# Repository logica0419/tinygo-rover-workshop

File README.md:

# tinygo-rover-workshop

TinyGo Rover Workshop 〜走れ！Tiny号

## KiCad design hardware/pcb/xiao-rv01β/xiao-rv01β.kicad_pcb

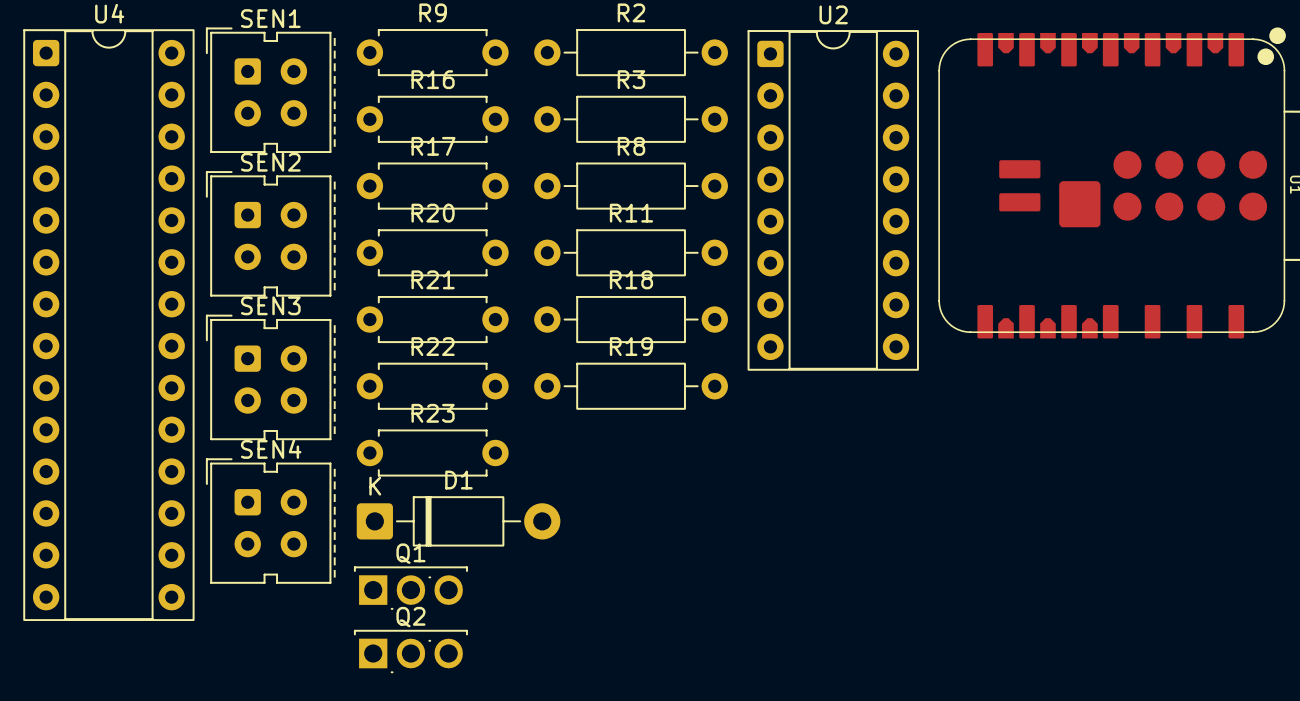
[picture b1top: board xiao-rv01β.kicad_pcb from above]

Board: 2 copper layers, 23 parts (0 on the bottom side), 21 nets, no tracks yet.

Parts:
D1: TVS 5V; D_DO-41_SOD81_P10.16mm_Horizontal
Q1, Q2: P-Ch -12V/-6A; TO-251-3_Vertical
R2, R19: 100kΩ; R_Axial_DIN0207_L6.3mm_D2.5mm_P10.16mm_Horizontal
R3, R8, R11: 22kΩ; R_Axial_DIN0207_L6.3mm_D2.5mm_P10.16mm_Horizontal
R9, R16, R17, R20, R23: 2.2kΩ; R_Axial_DIN0207_L6.3mm_D2.5mm_P7.62mm_Horizontal
R18: 33kΩ; R_Axial_DIN0207_L6.3mm_D2.5mm_P10.16mm_Horizontal
R21, R22: 1kΩ; R_Axial_DIN0207_L6.3mm_D2.5mm_P7.62mm_Horizontal
SEN1, SEN2, SEN3, SEN4: LBR-123F; Vishay_CNY70
U1: XIAO-ESP32-S3-Plus; XIAO-ESP32-S3-Plus-SMD
U2: MCP3208; DIP-16_W7.62mm_Socket
U4: MCP23S17; DIP-28_W7.62mm_Socket

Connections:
3V3: R9.1, R16.1, R17.1, R20.1, SEN1.3 (C), SEN2.3 (C), SEN3.3 (C), SEN4.3 (C), U1.12 (3V3), U2.15 (Vref), U2.16 (Vdd), U4.9 (V_{DD}), U4.18 (~RESET)
ADC_CS: R20.2, U1.20 (GPIO10_XMCLK_ADC_BAT), U2.10 (~CS/SHDN)
BUZZER: R22.2, U1.8 (GPIO44_D7_RX)
GND: D1.2 (A), R2.2, R18.2, R21.1, R23.1, SEN1.2 (K), SEN2.2 (K), SEN3.2 (K), SEN4.2 (K), U1.13 (GND), U1.33 (GND2), U1.34 (PAD), U2.9 (DGND), U2.14 (AGND), U4.10 (V_{SS}), U4.15 (A0), U4.16 (A1), U4.17 (A2)
IOE_CS: R17.2, U1.19 (GPIO42_PDM_CLK_TX1), U4.11 (~CS)
MISO: U1.10 (GPIO8_A9_D9_MISO), U2.12 (Dout), U4.14 (SO)
MOSI: U1.11 (GPIO9_A10_D10_MOSI), U2.11 (Din), U4.13 (SI)
unnamed: D1.1 (K), Q1.3 (S), Q2.2 (D), U1.32 (VBAT)
unnamed: Q1.1 (G), R2.1, R3.1
unnamed: Q2.1 (G), R19.2
unnamed: Q2.3 (S), R19.1
unnamed: SEN1.4 (E), U2.4 (CH3)
unnamed: SEN2.4 (E), U2.3 (CH2)
unnamed: SEN3.4 (E), U2.2 (CH1)
unnamed: SEN4.4 (E), U2.1 (CH0)
unnamed: R8.2, U1.1 (GPIO1_A0_D0)
unnamed: R11.2, R18.1, U1.21 (GPIO11_DVP_Y8_SPI_MOSI1)
SCK: U1.9 (GPIO7_A8_D8_SCK), U2.13 (CLK), U4.12 (SCK)
SCL: R16.2, U1.18 (GPIO41_PDM_DATA_RX1)
SDA: R9.2, U1.17 (GPIO40_CAM_SDA_I2S_WS)
VBUS: R3.2, R11.1, U1.14 (VBUS)

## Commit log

2026-06-01 initialize pcb directory
2026-06-01 open KiCad on Windows
2026-06-02 designed power/mcu/motor driver schematic
2026-06-03 completed the 1st edit of xiao-rv01β
2026-06-04 add power switch & organize
2026-06-04 tweak
2026-06-04 modified distance sensor & tweaks
2026-06-05 initialize PCB
2026-06-09 switched to xiao esp32s3 plus & SPI-based expansion
2026-06-11 add DCDC converter
2026-06-12 fix ICs
2026-06-14 use CSD87501L for battery protection mosfet
